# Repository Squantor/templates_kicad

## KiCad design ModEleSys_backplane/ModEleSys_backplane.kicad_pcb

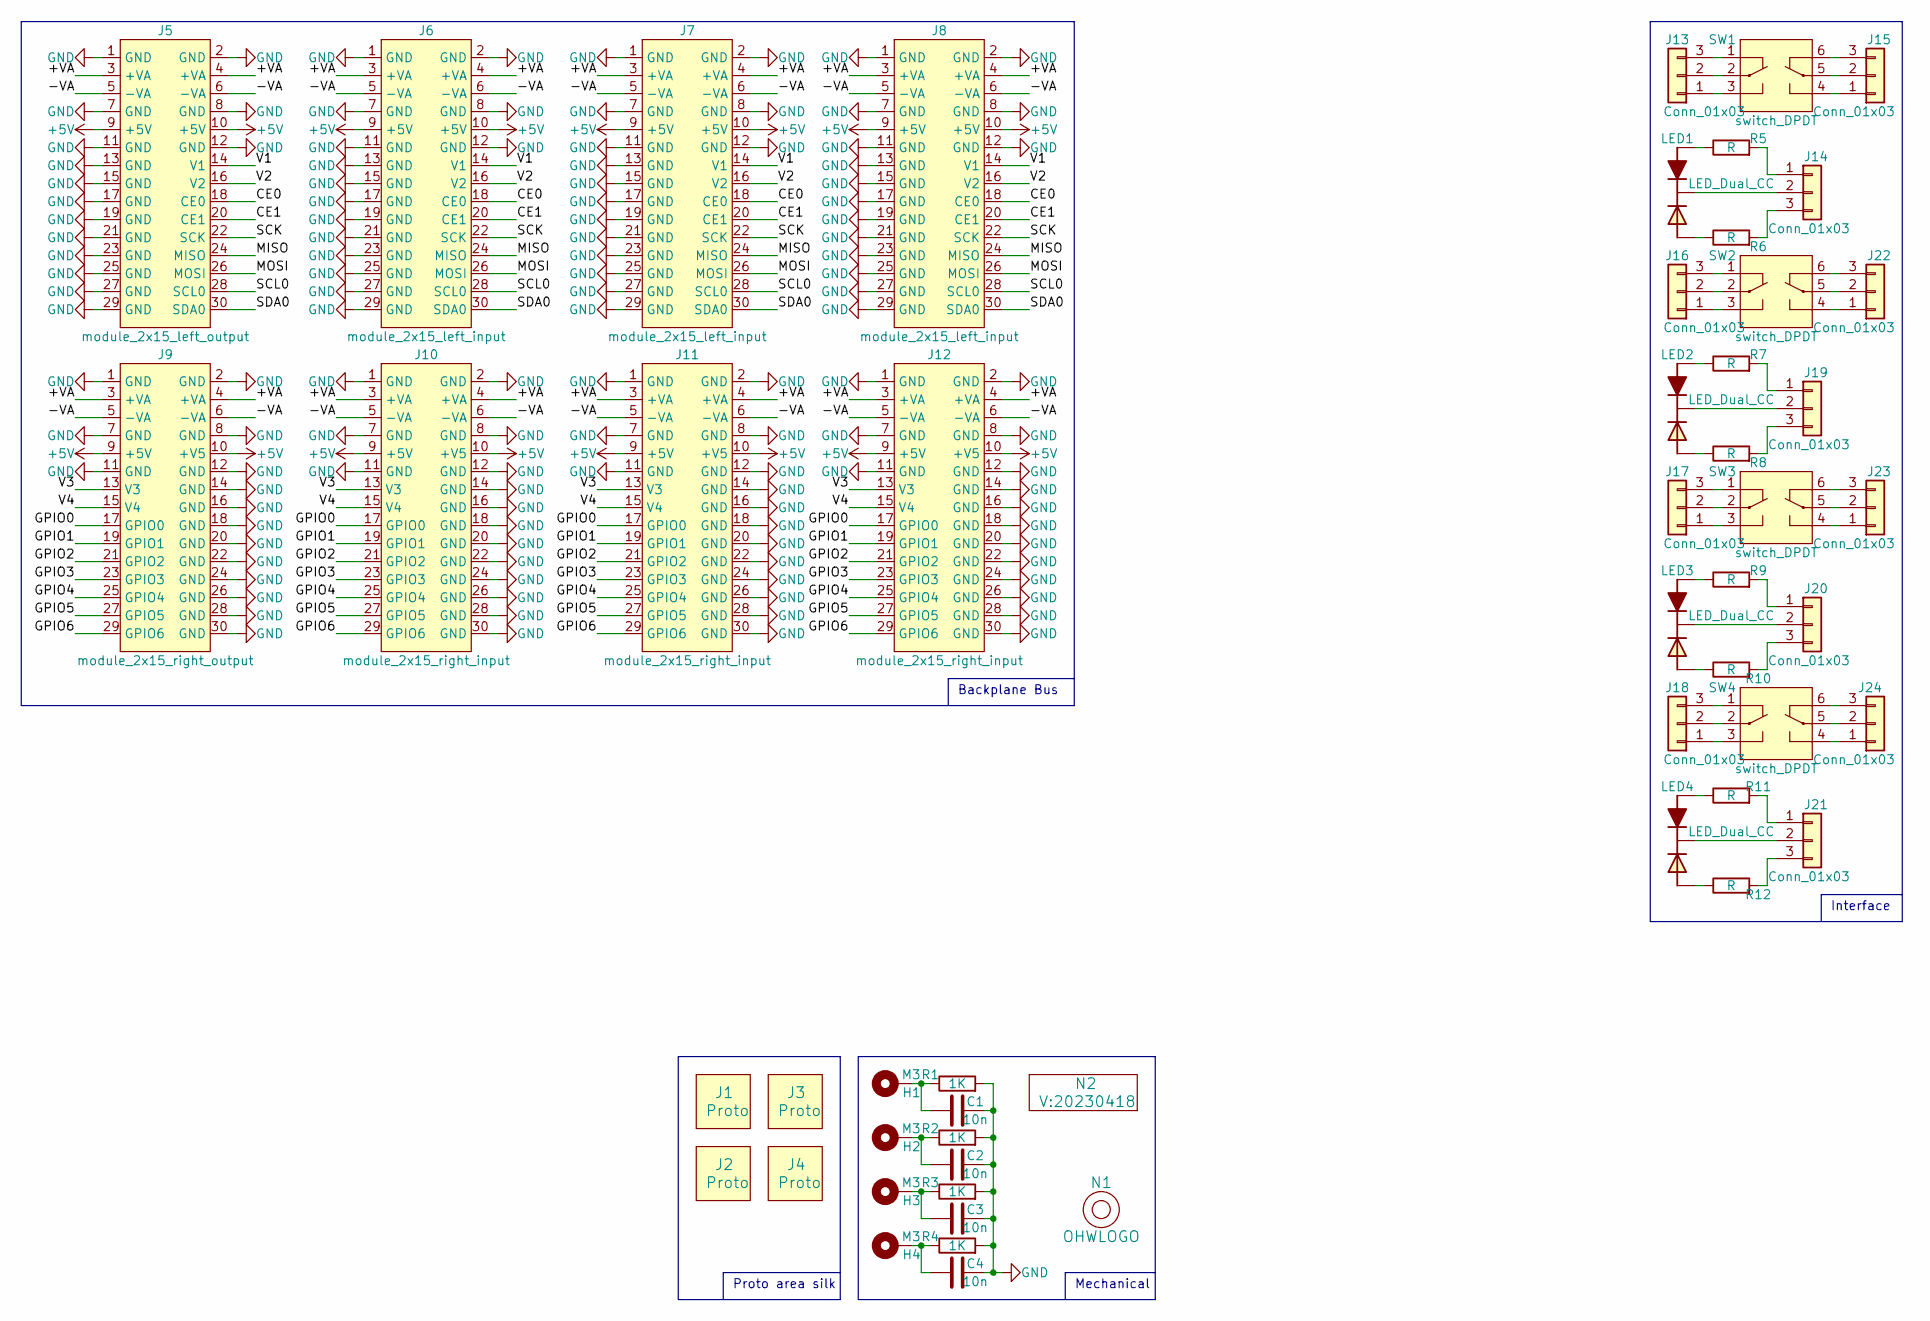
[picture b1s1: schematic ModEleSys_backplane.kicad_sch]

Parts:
C1, C2, C3, C4: 10n; C_0805+0603
H1, H2, H3, H4: M3; MountingHole_3.2mm_M3_Pad_Via
J1, J2, J3, J4: Proto; 4by4cm_module
J5: module_2x15_left_output; module_2x15_left
J6, J7, J8: module_2x15_left_input; module_2x15_left
J9: module_2x15_right_output; module_2x15_right
J10, J11, J12: module_2x15_right_input; module_2x15_right
J13, J14, J15, J16, J17, J18, J19, J20, J21, J22, J23, J24: Conn_01x03; JST_PH_B3B-PH-K_1x03_P2.00mm_Vertical
LED1, LED2, LED3, LED4: LED_Dual_CC; LED_DUAL_TH245_90deg
N1: OHWLOGO; OSHW-Symbol_6.7x6mm_SilkScreen
N2: V:20230418; Label_Generic
R1, R2, R3, R4: 1K; R_0805+0603
R5, R6, R7, R8, R9, R10, R11, R12: R; R_0603_hand
SW1, SW2, SW3, SW4: switch_DPDT; PS-22F02

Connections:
+5V: J5.9 (+5V), J5.10 (+5V), J6.9 (+5V), J6.10 (+5V), J7.9 (+5V), J7.10 (+5V), J8.9 (+5V), J8.10 (+5V), J9.9 (+5V), J9.10 (+V5), J10.9 (+5V), J10.10 (+V5), J11.9 (+5V), J11.10 (+V5), J12.9 (+5V), J12.10 (+V5)
/+VA: J5.3 (+VA), J5.4 (+VA), J6.3 (+VA), J6.4 (+VA), J7.3 (+VA), J7.4 (+VA), J8.3 (+VA), J8.4 (+VA), J9.3 (+VA), J9.4 (+VA), J10.3 (+VA), J10.4 (+VA), J11.3 (+VA), J11.4 (+VA), J12.3 (+VA), J12.4 (+VA)
/-VA: J5.5 (-VA), J5.6 (-VA), J6.5 (-VA), J6.6 (-VA), J7.5 (-VA), J7.6 (-VA), J8.5 (-VA), J8.6 (-VA), J9.5 (-VA), J9.6 (-VA), J10.5 (-VA), J10.6 (-VA), J11.5 (-VA), J11.6 (-VA), J12.5 (-VA), J12.6 (-VA)
/CE0: J5.18 (CE0), J6.18 (CE0), J7.18 (CE0), J8.18 (CE0)
/CE1: J5.20 (CE1), J6.20 (CE1), J7.20 (CE1), J8.20 (CE1)
/GPIO0: J9.17 (GPIO0), J10.17 (GPIO0), J11.17 (GPIO0), J12.17 (GPIO0)
/GPIO1: J9.19 (GPIO1), J10.19 (GPIO1), J11.19 (GPIO1), J12.19 (GPIO1)
/GPIO2: J9.21 (GPIO2), J10.21 (GPIO2), J11.21 (GPIO2), J12.21 (GPIO2)
/GPIO3: J9.23 (GPIO3), J10.23 (GPIO3), J11.23 (GPIO3), J12.23 (GPIO3)
/GPIO4: J9.25 (GPIO4), J10.25 (GPIO4), J11.25 (GPIO4), J12.25 (GPIO4)
/GPIO5: J9.27 (GPIO5), J10.27 (GPIO5), J11.27 (GPIO5), J12.27 (GPIO5)
/GPIO6: J9.29 (GPIO6), J10.29 (GPIO6), J11.29 (GPIO6), J12.29 (GPIO6)
/MISO: J5.24 (MISO), J6.24 (MISO), J7.24 (MISO), J8.24 (MISO)
/MOSI: J5.26 (MOSI), J6.26 (MOSI), J7.26 (MOSI), J8.26 (MOSI)
/SCK: J5.22 (SCK), J6.22 (SCK), J7.22 (SCK), J8.22 (SCK)
/SCL0: J5.28 (SCL0), J6.28 (SCL0), J7.28 (SCL0), J8.28 (SCL0)
/SDA0: J5.30 (SDA0), J6.30 (SDA0), J7.30 (SDA0), J8.30 (SDA0)
/V1: J5.14 (V1), J6.14 (V1), J7.14 (V1), J8.14 (V1)
/V2: J5.16 (V2), J6.16 (V2), J7.16 (V2), J8.16 (V2)
/V3: J9.13 (V3), J10.13 (V3), J11.13 (V3), J12.13 (V3)
/V4: J9.15 (V4), J10.15 (V4), J11.15 (V4), J12.15 (V4)
GND: C1.2, C2.2, C3.2, C4.2, J5.1 (GND), J5.2 (GND), J5.7 (GND), J5.8 (GND), J5.11 (GND), J5.12 (GND), J5.13 (GND), J5.15 (GND), J5.17 (GND), J5.19 (GND), J5.21 (GND), J5.23 (GND), J5.25 (GND), J5.27 (GND), J5.29 (GND), J6.1 (GND), J6.2 (GND), J6.7 (GND), J6.8 (GND), J6.11 (GND), J6.12 (GND), J6.13 (GND), J6.15 (GND), J6.17 (GND), J6.19 (GND), J6.21 (GND), J6.23 (GND), J6.25 (GND), J6.27 (GND), J6.29 (GND), J7.1 (GND), J7.2 (GND), J7.7 (GND), J7.8 (GND), J7.11 (GND), J7.12 (GND), J7.13 (GND), J7.15 (GND), J7.17 (GND), J7.19 (GND), J7.21 (GND), J7.23 (GND), J7.25 (GND), J7.27 (GND), J7.29 (GND), J8.1 (GND), J8.2 (GND), J8.7 (GND), J8.8 (GND), J8.11 (GND), J8.12 (GND), J8.13 (GND), J8.15 (GND), J8.17 (GND), J8.19 (GND), J8.21 (GND), J8.23 (GND), J8.25 (GND), J8.27 (GND), J8.29 (GND), J9.1 (GND), J9.2 (GND), J9.7 (GND), J9.8 (GND), J9.11 (GND), J9.12 (GND), J9.14 (GND), J9.16 (GND), J9.18 (GND), J9.20 (GND), J9.22 (GND), J9.24 (GND), J9.26 (GND), J9.28 (GND), J9.30 (GND), J10.1 (GND), J10.2 (GND), J10.7 (GND), J10.8 (GND), J10.11 (GND), J10.12 (GND), J10.14 (GND), J10.16 (GND), J10.18 (GND), J10.20 (GND), J10.22 (GND), J10.24 (GND), J10.26 (GND), J10.28 (GND), J10.30 (GND), J11.1 (GND), J11.2 (GND), J11.7 (GND), J11.8 (GND), J11.11 (GND), J11.12 (GND), J11.14 (GND), J11.16 (GND), J11.18 (GND), J11.20 (GND), J11.22 (GND), J11.24 (GND), J11.26 (GND), J11.28 (GND), J11.30 (GND), J12.1 (GND), J12.2 (GND), J12.7 (GND), J12.8 (GND), J12.11 (GND), J12.12 (GND), J12.14 (GND), J12.16 (GND), J12.18 (GND), J12.20 (GND), J12.22 (GND), J12.24 (GND), J12.26 (GND), J12.28 (GND), J12.30 (GND), R1.2, R2.2, R3.2, R4.2
unnamed: C1.1, H1.1, R1.1
unnamed: C2.1, H2.1, R2.1
unnamed: C3.1, H3.1, R3.1
unnamed: C4.1, H4.1, R4.1
unnamed: J13.1, SW1.3 (SW1_P2)
unnamed: J13.2, SW1.2 (SW1_C1)
unnamed: J13.3, SW1.1 (SW1_P1)
unnamed: J14.1, R5.2
unnamed: J14.2, LED1.2 (C)
unnamed: J14.3, R6.2
unnamed: J15.1, SW1.4 (SW2_P2)
unnamed: J15.2, SW1.5 (SW2_C1)
unnamed: J15.3, SW1.6 (SW2_P2)
unnamed: J16.1, SW2.3 (SW1_P2)
unnamed: J16.2, SW2.2 (SW1_C1)
unnamed: J16.3, SW2.1 (SW1_P1)
unnamed: J17.1, SW3.3 (SW1_P2)
unnamed: J17.2, SW3.2 (SW1_C1)
unnamed: J17.3, SW3.1 (SW1_P1)
unnamed: J18.1, SW4.3 (SW1_P2)
unnamed: J18.2, SW4.2 (SW1_C1)
unnamed: J18.3, SW4.1 (SW1_P1)
unnamed: J19.1, R7.2
unnamed: J19.2, LED2.2 (C)
unnamed: J19.3, R8.2
unnamed: J20.1, R9.2
unnamed: J20.2, LED3.2 (C)
unnamed: J20.3, R10.2
unnamed: J21.1, R11.2
unnamed: J21.2, LED4.2 (C)
unnamed: J21.3, R12.2
unnamed: J22.1, SW2.4 (SW2_P2)
unnamed: J22.2, SW2.5 (SW2_C1)
unnamed: J22.3, SW2.6 (SW2_P2)
unnamed: J23.1, SW3.4 (SW2_P2)
unnamed: J23.2, SW3.5 (SW2_C1)
unnamed: J23.3, SW3.6 (SW2_P2)
unnamed: J24.1, SW4.4 (SW2_P2)
unnamed: J24.2, SW4.5 (SW2_C1)
unnamed: J24.3, SW4.6 (SW2_P2)
unnamed: LED1.1 (A1), R5.1
unnamed: LED1.3 (A2), R6.1
unnamed: LED2.1 (A1), R7.1
unnamed: LED2.3 (A2), R8.1
unnamed: LED3.1 (A1), R9.1
unnamed: LED3.3 (A2), R10.1
unnamed: LED4.1 (A1), R11.1
unnamed: LED4.3 (A2), R12.1

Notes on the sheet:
Proto area silk
Interface
Mechanical
Backplane Bus

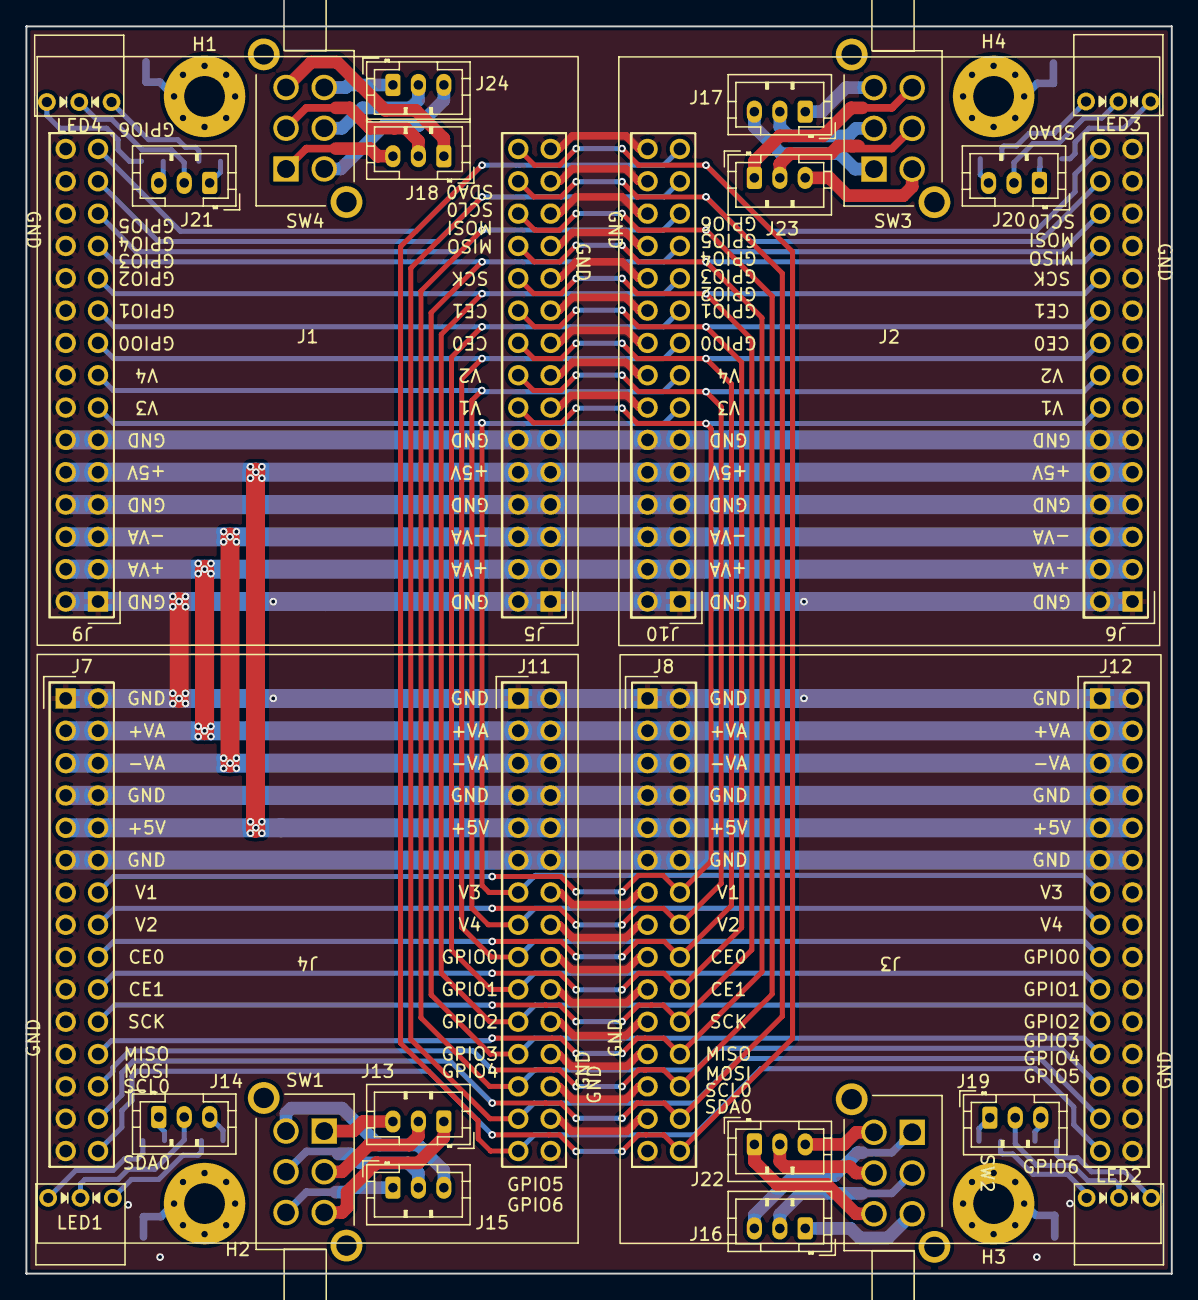
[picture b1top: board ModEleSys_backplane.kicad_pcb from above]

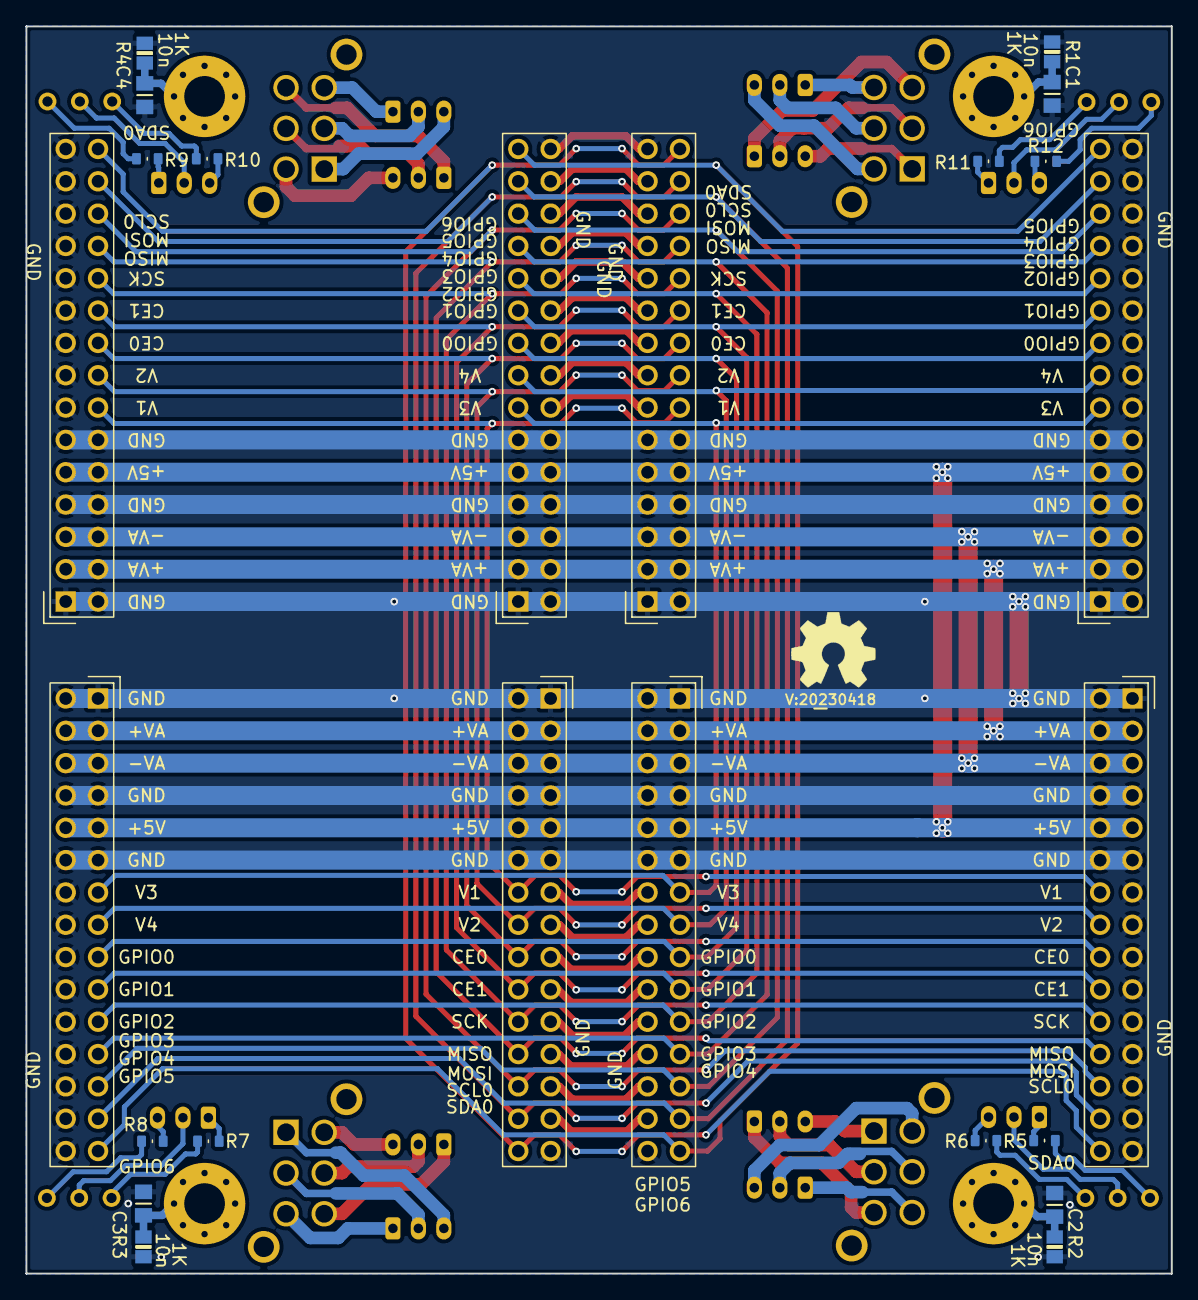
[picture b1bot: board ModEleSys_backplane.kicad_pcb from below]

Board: 2 copper layers, 90.0 x 98.0 mm, 54 parts (18 on the bottom side), 70 nets.

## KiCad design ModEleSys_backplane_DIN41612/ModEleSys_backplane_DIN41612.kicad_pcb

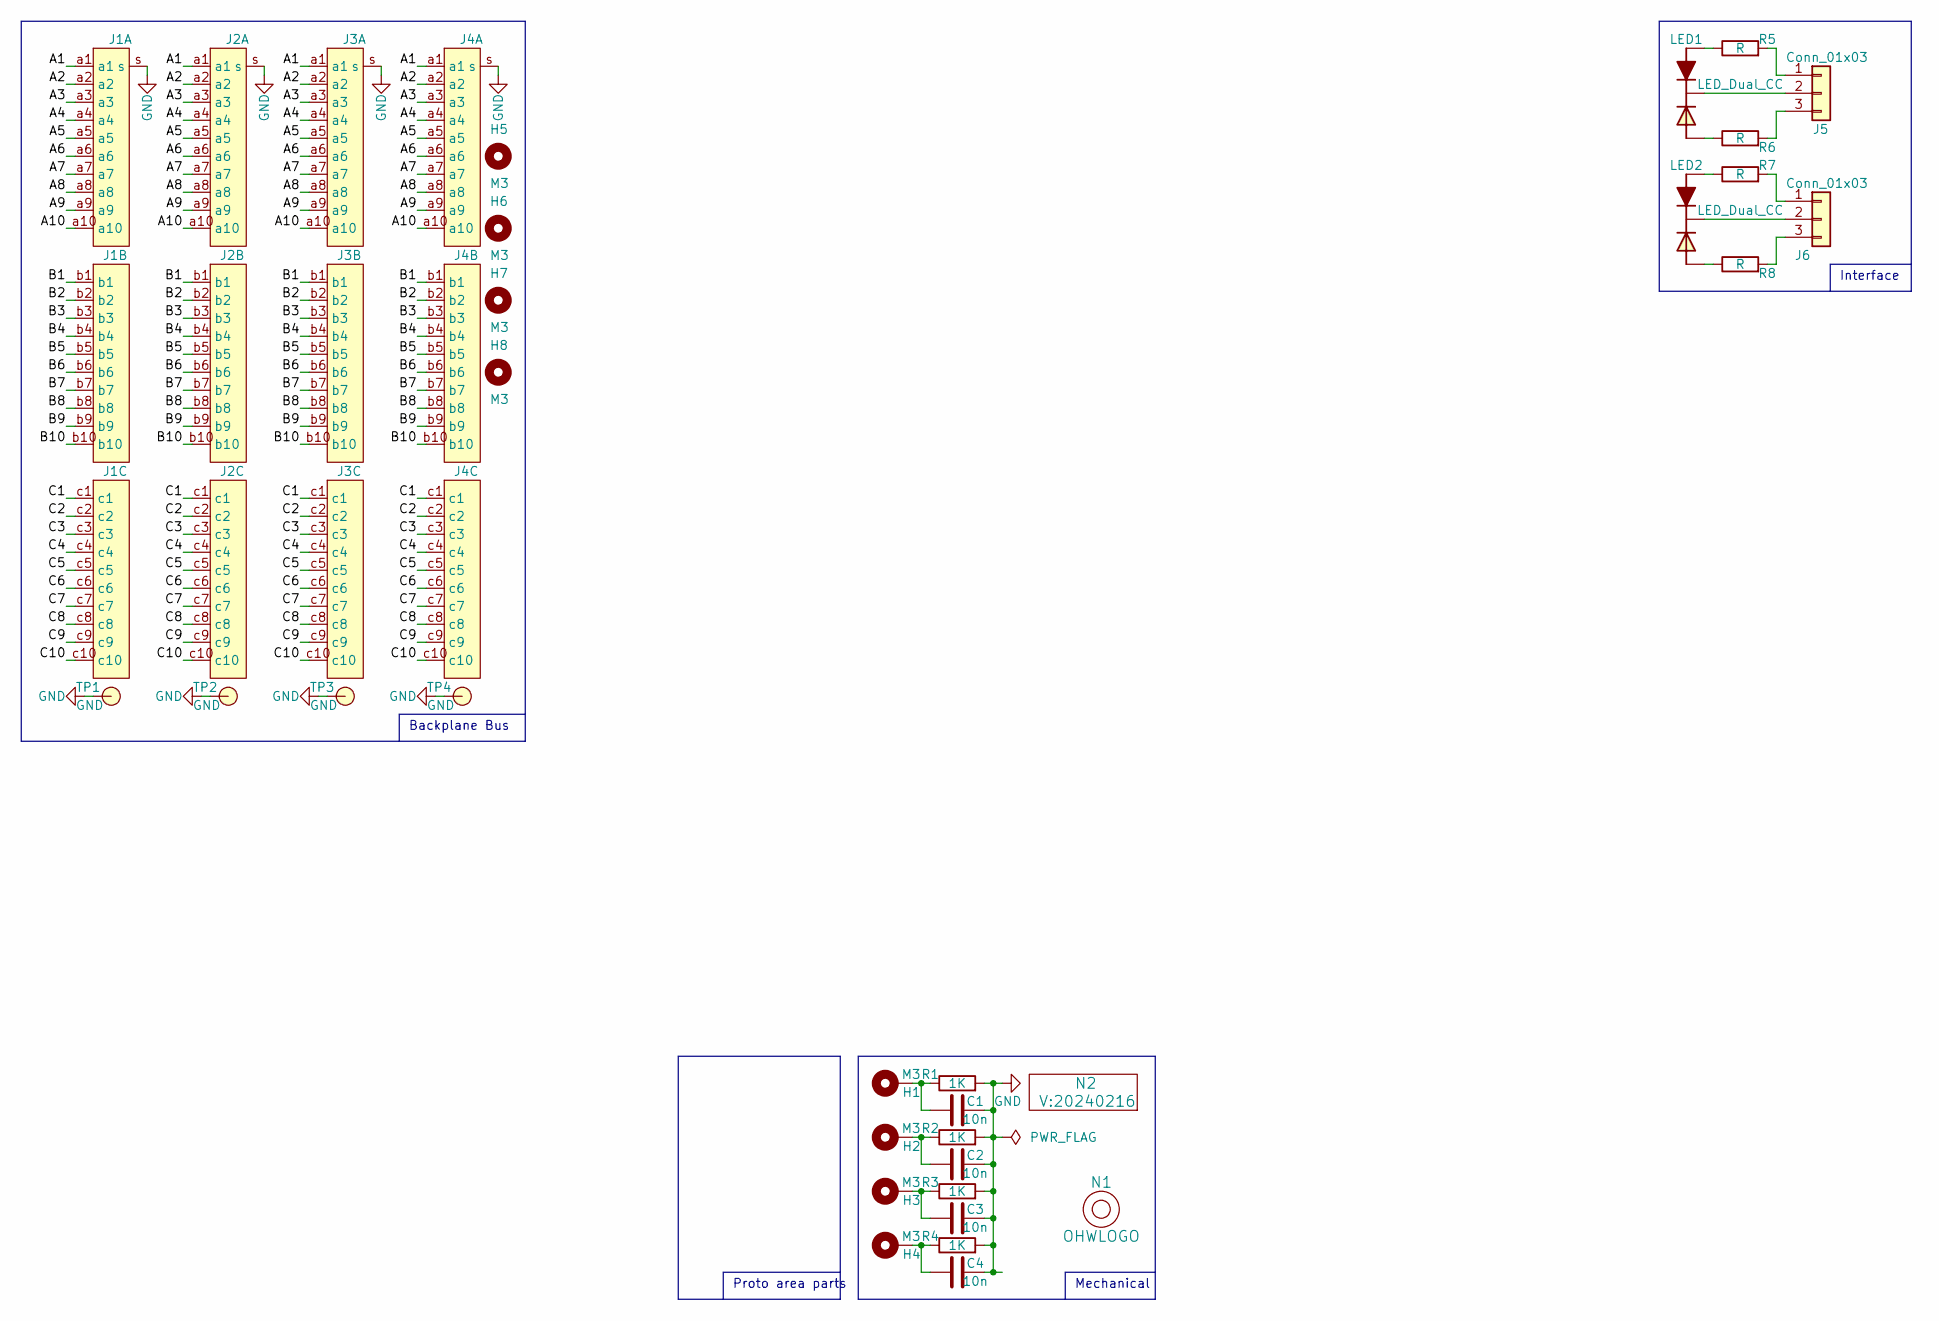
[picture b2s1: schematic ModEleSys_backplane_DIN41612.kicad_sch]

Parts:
C1, C2, C3, C4: 10n; C_0805+0603
H1, H2, H3, H4, H5, H6, H7, H8: M3; MountingHole_3.2mm_M3_Pad_Via
J1, J2, J3, J4: DIN41612_C3_3x10_Female_Vertical_THT_shields
J5, J6: Conn_01x03; JST_PH_B3B-PH-K_1x03_P2.00mm_Vertical
LED1, LED2: LED_Dual_CC; LED_DUAL_TH245_90deg
N1: OHWLOGO; OSHW-Symbol_6.7x6mm_SilkScreen
N2: V:20240216; Label_Generic
R1, R2, R3, R4: 1K; R_0805+0603
R5, R6, R7, R8: R; R_0603_hand
TP1, TP2, TP3, TP4: GND; TestPoint_hole_H05R10

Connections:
/A1: J1.a1, J2.a1, J3.a1, J4.a1
/A2: J1.a2, J2.a2, J3.a2, J4.a2
/A3: J1.a3, J2.a3, J3.a3, J4.a3
/A4: J1.a4, J2.a4, J3.a4, J4.a4
/A5: J1.a5, J2.a5, J3.a5, J4.a5
/A6: J1.a6, J2.a6, J3.a6, J4.a6
/A7: J1.a7, J2.a7, J3.a7, J4.a7
/A8: J1.a8, J2.a8, J3.a8, J4.a8
/A9: J1.a9, J2.a9, J3.a9, J4.a9
/A10: J1.a10, J2.a10, J3.a10, J4.a10
/B1: J1.b1, J2.b1, J3.b1, J4.b1
/B2: J1.b2, J2.b2, J3.b2, J4.b2
/B3: J1.b3, J2.b3, J3.b3, J4.b3
/B4: J1.b4, J2.b4, J3.b4, J4.b4
/B5: J1.b5, J2.b5, J3.b5, J4.b5
/B6: J1.b6, J2.b6, J3.b6, J4.b6
/B7: J1.b7, J2.b7, J3.b7, J4.b7
/B8: J1.b8, J2.b8, J3.b8, J4.b8
/B9: J1.b9, J2.b9, J3.b9, J4.b9
/B10: J1.b10, J2.b10, J3.b10, J4.b10
/C1: J1.c1, J2.c1, J3.c1, J4.c1
/C2: J1.c2, J2.c2, J3.c2, J4.c2
/C3: J1.c3, J2.c3, J3.c3, J4.c3
/C4: J1.c4, J2.c4, J3.c4, J4.c4
/C5: J1.c5, J2.c5, J3.c5, J4.c5
/C6: J1.c6, J2.c6, J3.c6, J4.c6
/C7: J1.c7, J2.c7, J3.c7, J4.c7
/C8: J1.c8, J2.c8, J3.c8, J4.c8
/C9: J1.c9, J2.c9, J3.c9, J4.c9
/C10: J1.c10, J2.c10, J3.c10, J4.c10
GND: C1.2, C2.2, C3.2, C4.2, J1.s, J2.s, J3.s, J4.s, R1.2, R2.2, R3.2, R4.2, TP1.1, TP2.1, TP3.1, TP4.1
unnamed: C1.1, H1.1, R1.1
unnamed: C2.1, H2.1, R2.1
unnamed: C3.1, H3.1, R3.1
unnamed: C4.1, H4.1, R4.1
unnamed: J5.1, R5.2
unnamed: J5.2, LED1.2 (C)
unnamed: J5.3, R6.2
unnamed: J6.1, R7.2
unnamed: J6.2, LED2.2 (C)
unnamed: J6.3, R8.2
unnamed: LED1.1 (A1), R5.1
unnamed: LED1.3 (A2), R6.1
unnamed: LED2.1 (A1), R7.1
unnamed: LED2.3 (A2), R8.1

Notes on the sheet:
Proto area parts
Mechanical
Interface
Backplane Bus

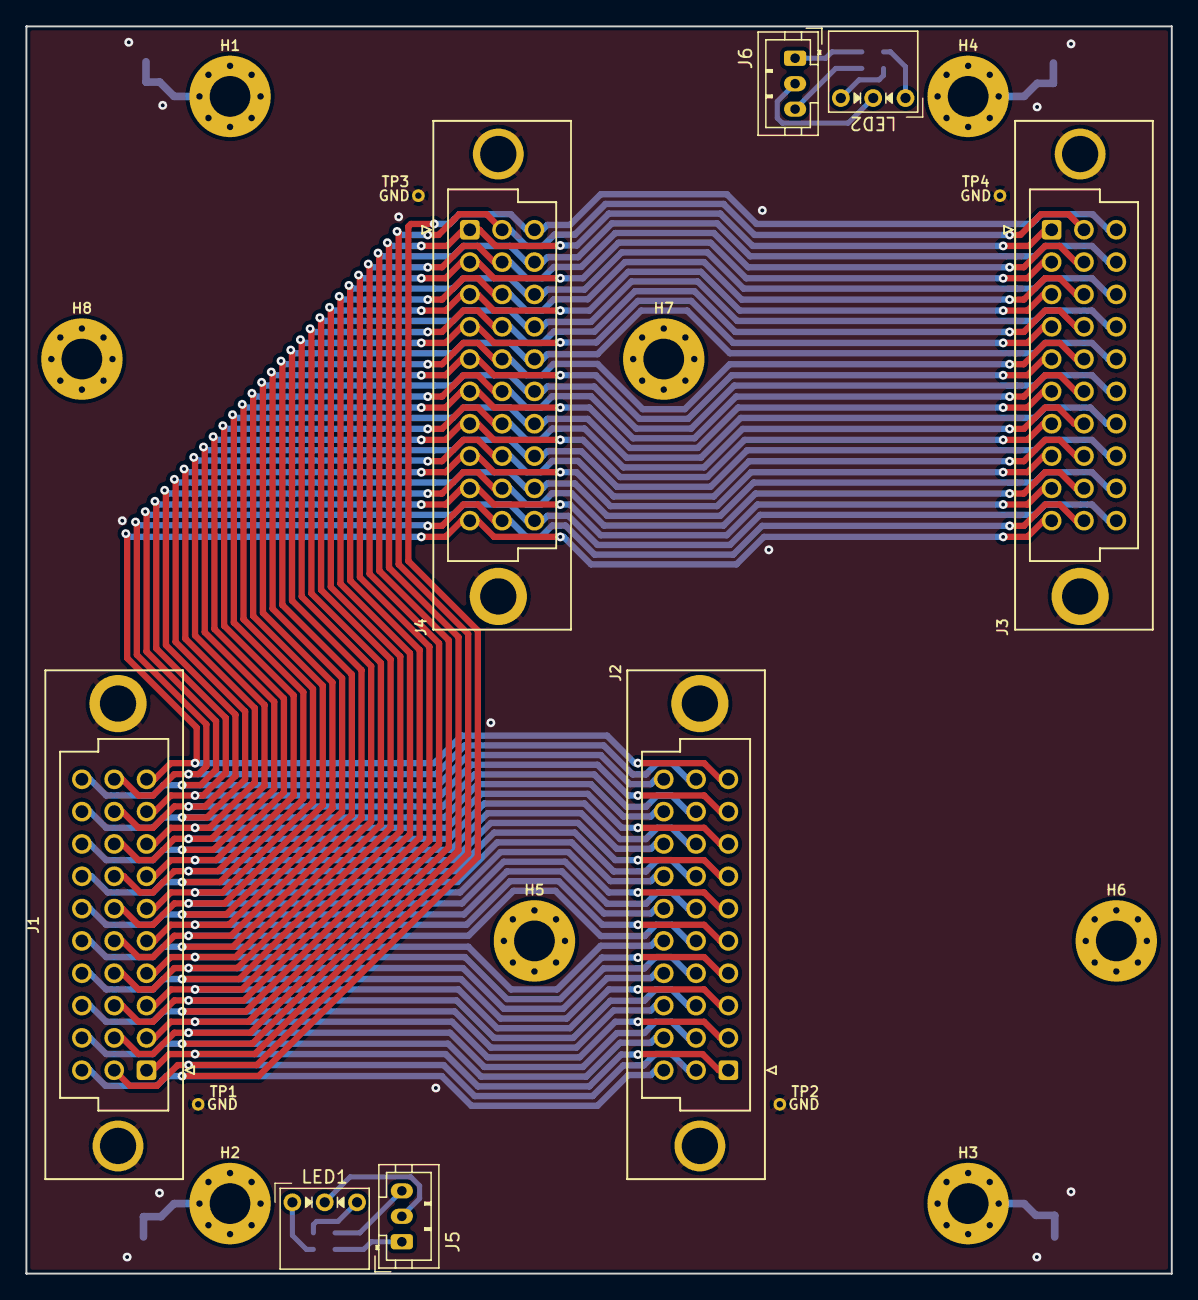
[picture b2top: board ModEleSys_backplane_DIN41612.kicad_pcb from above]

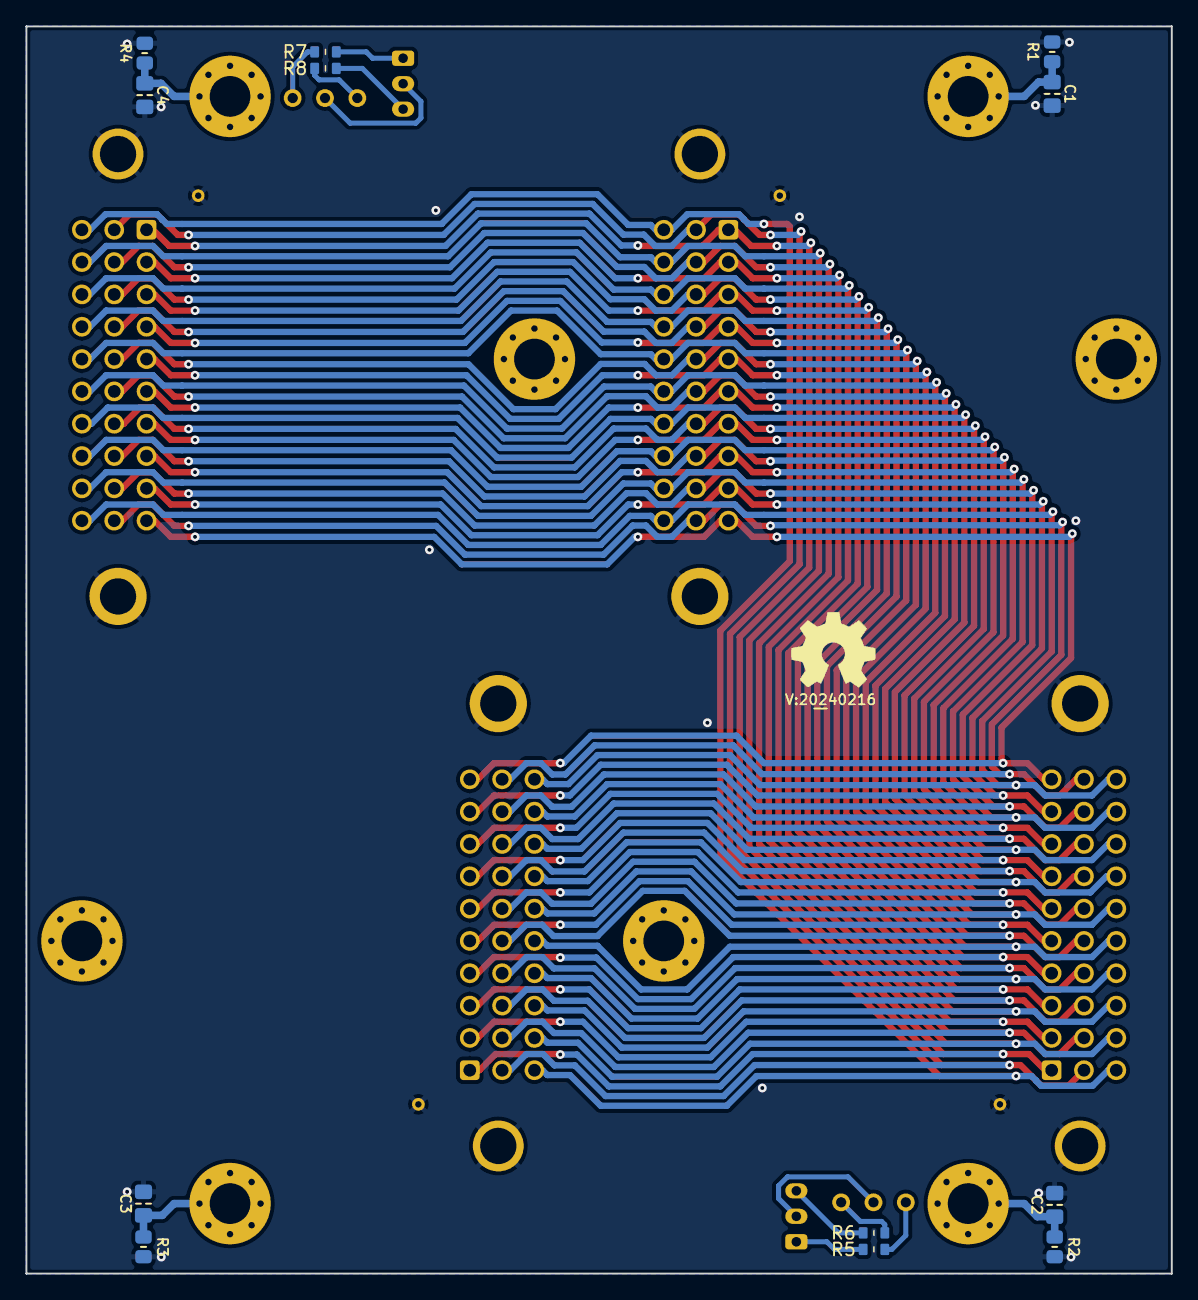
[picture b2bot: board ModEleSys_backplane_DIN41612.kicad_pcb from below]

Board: 2 copper layers, 90.0 x 98.0 mm, 34 parts (14 on the bottom side), 45 nets.
